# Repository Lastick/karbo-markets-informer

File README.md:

This device is a hardware informer for the market. Essentially, it works using the MQTT protocol for external communication. To operate, you need an
external power source with a rated operating voltage of 5V and a rated output current of at least 1 A. This version of the informer also works using
wireless Wi-Fi technology, which may affect sanitary standards of operation.

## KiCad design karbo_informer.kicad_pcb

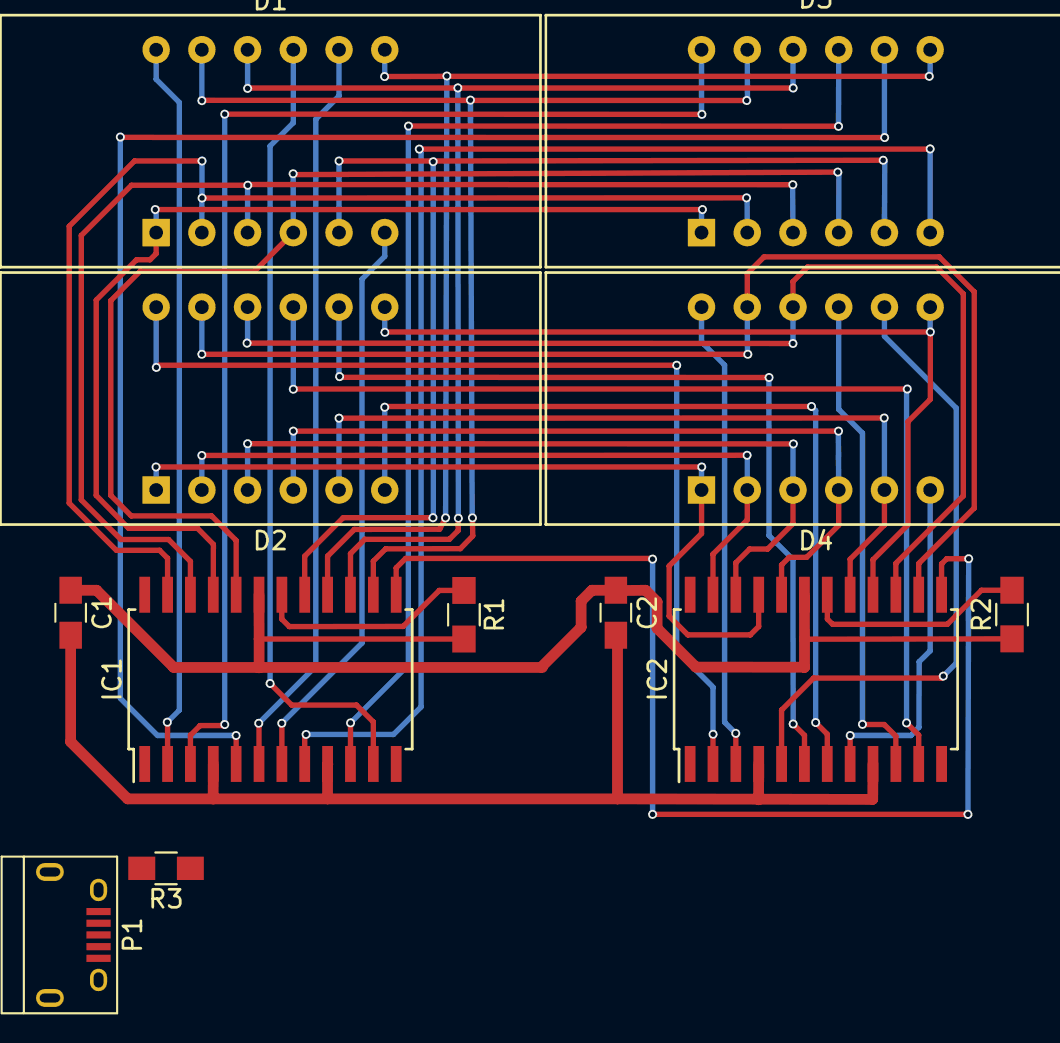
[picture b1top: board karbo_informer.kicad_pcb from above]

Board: 2 copper layers, 12 parts (0 on the bottom side), 40 nets.

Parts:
C1, C2: C; C_0805_HandSoldering
D1, D2, D3, D4: SMA420364
IC1, IC2: MAX7219; SOIC-24W_7.5x15.4mm_Pitch1.27mm
P1: USB_OTG; USB_Micro-B
R1, R2: R; R_0805_HandSoldering
R3: 0 ohm; R_0805_HandSoldering

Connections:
/B_DIG_0: D1.12, IC1.2
/B_DIG_1: D1.9, IC1.11
/B_DIG_2: D1.8, IC1.6
/B_DIG_3: D1.6, IC1.7
/B_DIG_4: D3.12, IC1.3
/B_DIG_5: D3.9, IC1.10
/B_DIG_6: D3.8, IC1.5
/B_DIG_7: D3.6, IC1.8
/B_SEG_A: D1.11, D3.11, IC1.14
/B_SEG_B: D1.7, D3.7, IC1.16
/B_SEG_C: D1.4, D3.4, IC1.20
/B_SEG_D: D1.2, D3.2, IC1.23
/B_SEG_DP: D1.3, D3.3, IC1.22
/B_SEG_E: D1.1, D3.1, IC1.21
/B_SEG_F: D1.10, D3.10, IC1.15
/B_SEG_G: D1.5, D3.5, IC1.17
/S_DIG_0: D2.12, IC2.2
/S_DIG_1: D2.9, IC2.11
/S_DIG_2: D2.8, IC2.6
/S_DIG_3: D2.6, IC2.7
/S_DIG_4: D4.12, IC2.3
/S_DIG_5: D4.9, IC2.10
/S_DIG_6: D4.8, IC2.5
/S_DIG_7: D4.6, IC2.8
/S_SEG_A: D2.11, D4.11, IC2.14
/S_SEG_B: D2.7, D4.7, IC2.16
/S_SEG_C: D2.4, D4.4, IC2.20
/S_SEG_D: D2.2, D4.2, IC2.23
/S_SEG_DP: D2.3, D4.3, IC2.22
/S_SEG_E: D2.1, D4.1, IC2.21
/S_SEG_F: D2.10, D4.10, IC2.15
/S_SEG_G: D2.5, D4.5, IC2.17
GND: C1.2, C2.2, IC1.4, IC1.9, IC2.4, IC2.9, P1.5
unnamed: C1.1, C2.1, IC1.19, IC2.19, R1.2, R2.1, R3.1
unnamed: IC1.12, IC2.12
unnamed: IC1.13, IC2.13
unnamed: IC1.18, R1.1
unnamed: IC1.24, IC2.1
unnamed: IC2.18, R2.2
unnamed: P1.1, R3.2

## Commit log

2024-04-10 Replaced to Windows crlf
2024-04-10 Wire for segmant C (D2 to D4)
2024-04-10 Wire for segmant D (D2 to D4)
2024-04-10 Added licensing information in the LICENSE file
2024-04-10 Wire for segments C and DP in the sell line (D2 to D4)
2024-04-10 Wire for segments G in the sell line (D2 to D4)
2024-04-10 Wire for segments B in the sell line (D2 to D4)
2024-04-10 Wire for DIG0 and other in the buy line
2024-04-10 Wire for DIG2 to MAX7219 in the buy line
2024-04-10 Wire for DIG3 to MAX7219 in the buy line
2024-04-10 Wire for DIG1 to MAX7219 in the buy line
2024-04-10 Same update to buy line wires
2024-04-10 Wire for DIG4 to MAX7219 in the buy line
2024-04-10 Wire for DIG7 to MAX7219 in the buy line
2024-04-10 Wire for SEG_G to MAX7219 in the buy line
2024-04-10 Wire for SEG_B to MAX7219 in the buy line
2024-04-10 Wire for SEG_B to MAX7219 in the buy line (optimized)
2024-04-10 Wire for SEG_F to MAX7219 in the buy line
2024-04-10 Wire for SEG_A to MAX7219 in the buy line
2024-04-10 Wire for SEG_C to MAX7219 in the buy line
2024-04-10 Wire for SEG_E to MAX7219 in the buy line
2024-04-10 Wire for SEG_E to MAX7219 in the buy line (optimized)
2024-04-10 Wire for SEG_DP to MAX7219 in the buy line
2024-04-10 Wire for SEG_D to MAX7219 in the buy line
2024-04-10 Wire for DIG_3 to MAX7219 in the sell line
2024-04-10 Wire for DIG_2 to MAX7219 in the sell line
2024-04-10 Wire for DIG_1 to MAX7219 in the sell line
2024-04-10 Wire for DIG_4 to MAX7219 in the sell line
2024-04-10 Wire for DIG_5 to MAX7219 in the sell line
2024-04-10 Wire for DIG_7 to MAX7219 in the sell line
2024-04-10 Wire for DIG_6 to MAX7219 in the sell line
2024-04-10 Wire for all segments to MAX7219 in the sell line
2024-04-10 Wire for ref resistors (MAX7219)
2024-04-10 Wire for power supply (MAX7219)
2024-04-10 Same fix wires for R2 resistor
2024-04-10 Wire for connect sync of MAX7219 chips
2024-04-10 Optimized wire to DIG for bul line
2024-04-10 Forgeted line to VCC by REF resistor (IC1)
2024-04-10 Optimized power line VCC
2024-04-10 Removed bad wires for SEP_DP (buy)
2024-04-10 Optimized wire for REF resistor (buy line)
2024-04-10 Optimized location for through-hole (SEG_F of buy line)
2024-04-10 Optimized location for through-hole (SEG_G of buy line)
2024-04-10 Optimized location for through-hole (DIG_4 of buy line)
2024-04-10 Optimized location for through-hole (DIG_6 of buy line)
2024-04-10 Optimized wire for SEG_E (buy line)
2024-04-10 Optimized location for through-hole (SEG_A of buy line)
2024-04-10 Optimized location for through-hole (SEG_B of buy line)
2024-04-10 Optimized location for through-hole (DIG_1 of sell line)
2024-04-10 Optimized GND wire over MAX7219
2024-04-10 Optimized VCC wire MAX7219 (buy line)
2024-04-10 Optimized location for through-hole (SEG_B of sell line)
2024-04-10 Optimized VCC wire MAX7219 (sell line)
2024-04-10 Same more optimized VCC wire MAX7219 (sell line)
2024-04-10 Same more optimized VCC wire MAX7219 (buy line)
